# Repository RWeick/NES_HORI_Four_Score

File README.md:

# NES_HORI_Four_Score
The Kicad files for the NES HORI Four Score multitap adapter

PCB Thickness: 1.6 mm

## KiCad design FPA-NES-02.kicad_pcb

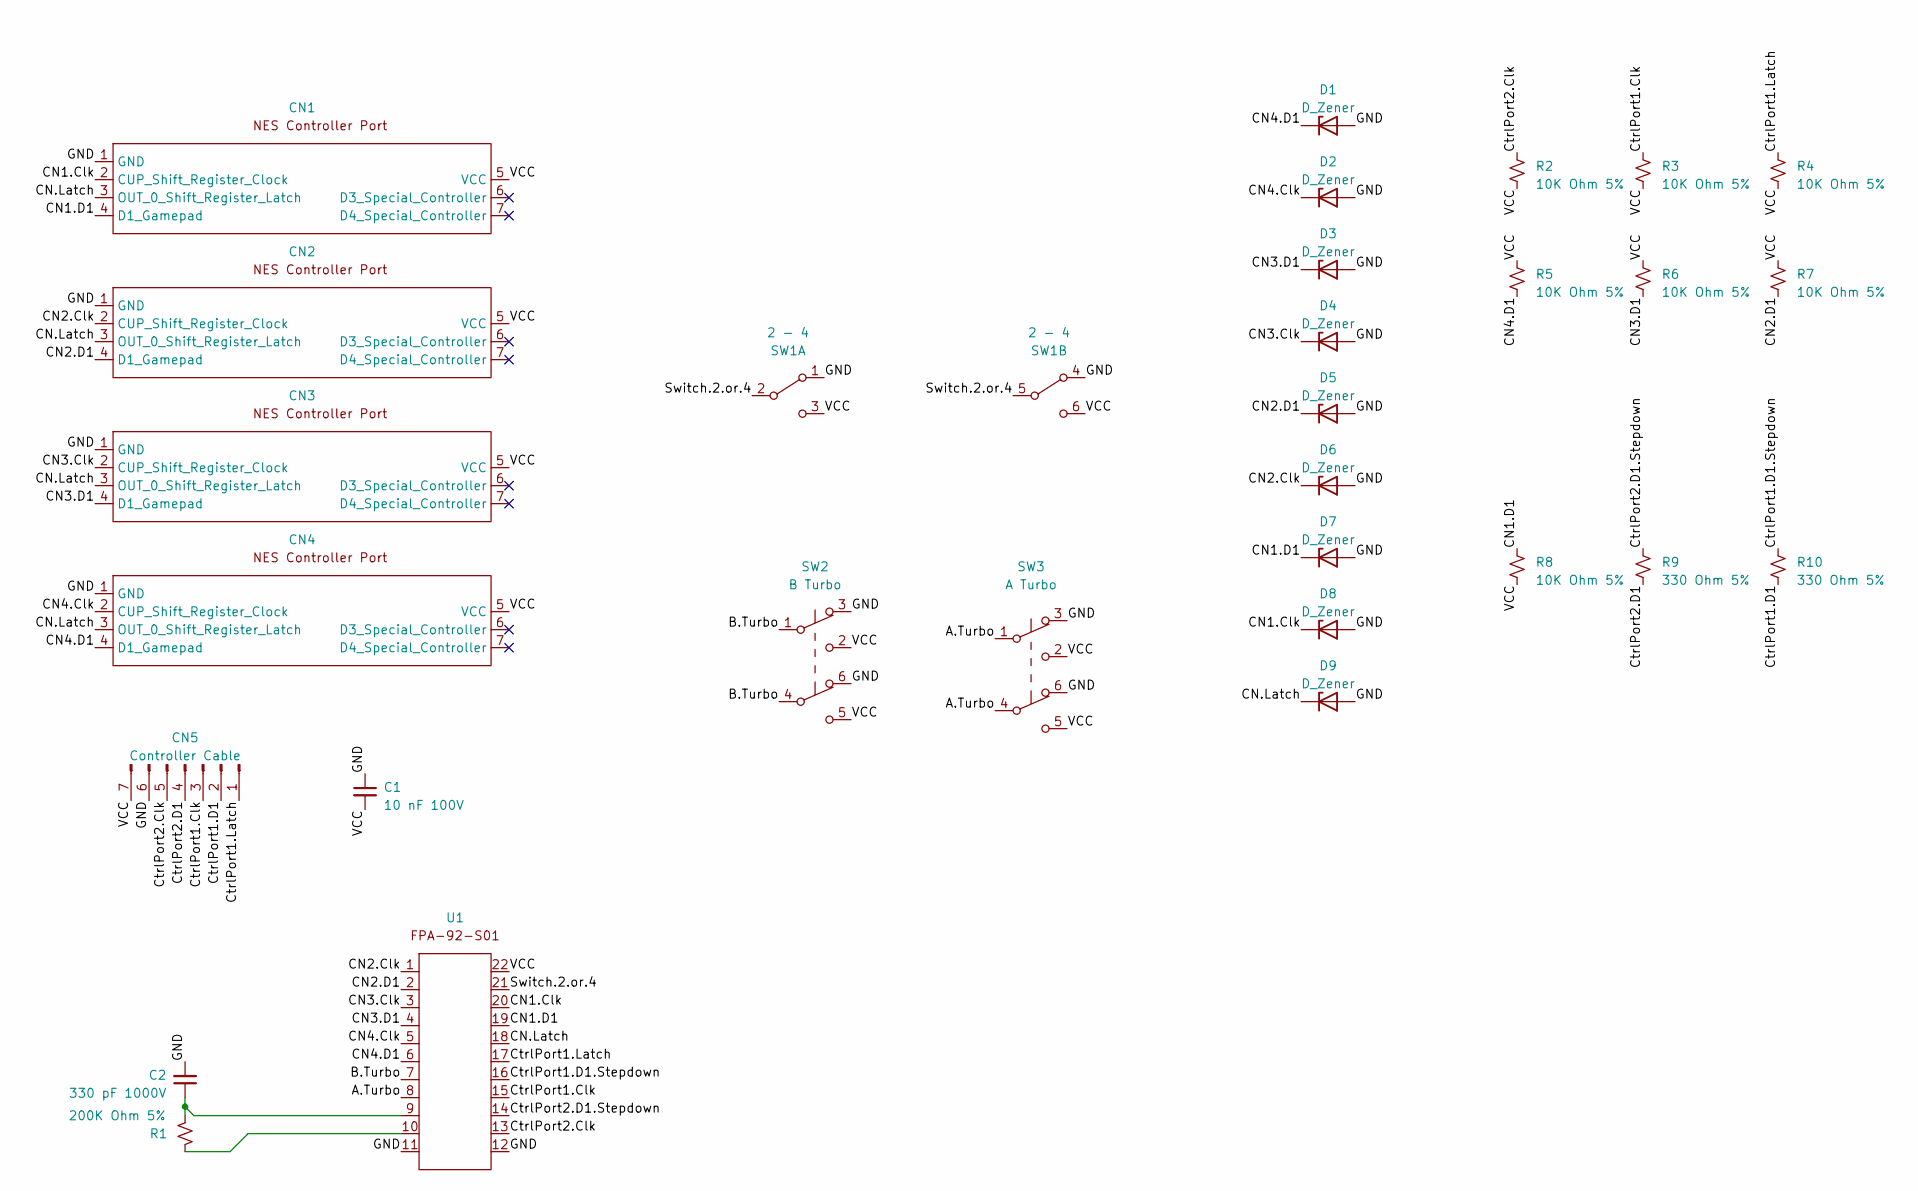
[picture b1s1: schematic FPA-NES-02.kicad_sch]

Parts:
C1: 10 nF 100V; Capacitor
C2: 330 pF 1000V; Capacitor
CN1, CN2, CN3, CN4: NES Controller Port
CN5: Controller Cable; NES Controller Port Connector
D1, D2, D3, D4, D5, D6, D7, D8, D9: D_Zener; Diode
R1: 200K Ohm 5%; Resistor
R2, R3, R4, R5, R6, R7, R8: 10K Ohm 5%; Resistor
R9, R10: 330 Ohm 5%; Resistor
SW1: 2 - 4; Slide Switch
SW2: B Turbo; Push Button Switch
SW3: A Turbo; Push Button Switch
U1: FPA-92-S01

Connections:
/A.Turbo: SW3.1 (B), SW3.4 (B), U1.8
/B.Turbo: SW2.1 (B), SW2.4 (B), U1.7
/CN1.Clk: CN1.2 (CUP_Shift_Register_Clock), D8.1 (K), U1.20
/CN1.D1: CN1.4 (D1_Gamepad), D7.1 (K), R8.1, U1.19
/CN2.Clk: CN2.2 (CUP_Shift_Register_Clock), D6.1 (K), U1.1
/CN2.D1: CN2.4 (D1_Gamepad), D5.1 (K), R7.2, U1.2
/CN3.Clk: CN3.2 (CUP_Shift_Register_Clock), D4.1 (K), U1.3
/CN3.D1: CN3.4 (D1_Gamepad), D3.1 (K), R6.2, U1.4
/CN4.Clk: CN4.2 (CUP_Shift_Register_Clock), D2.1 (K), U1.5
/CN4.D1: CN4.4 (D1_Gamepad), D1.1 (K), R5.2, U1.6
/CN.Latch: CN1.3 (OUT_0_Shift_Register_Latch), CN2.3 (OUT_0_Shift_Register_Latch), CN3.3 (OUT_0_Shift_Register_Latch), CN4.3 (OUT_0_Shift_Register_Latch), D9.1 (K), U1.18
/CtrlPort1.Clk: CN5.3, R3.1, U1.15
/CtrlPort1.D1: CN5.2, R10.2
/CtrlPort1.D1.Stepdown: R10.1, U1.16
/CtrlPort1.Latch: CN5.1, R4.1, U1.17
/CtrlPort2.Clk: CN5.5, R2.1, U1.13
/CtrlPort2.D1: CN5.4, R9.2
/CtrlPort2.D1.Stepdown: R9.1, U1.14
/GND: C1.1, C2.2, CN1.1 (GND), CN2.1 (GND), CN3.1 (GND), CN4.1 (GND), CN5.6, D1.2 (A), D2.2 (A), D3.2 (A), D4.2 (A), D5.2 (A), D6.2 (A), D7.2 (A), D8.2 (A), D9.2 (A), SW1.1 (A), SW1.4 (A), SW2.3 (A), SW2.6 (A), SW3.3 (A), SW3.6 (A), U1.11, U1.12
/Switch.2.or.4: SW1.2 (B), SW1.5 (B), U1.21
/VCC: C1.2, CN1.5 (VCC), CN2.5 (VCC), CN3.5 (VCC), CN4.5 (VCC), CN5.7, R2.2, R3.2, R4.2, R5.1, R6.1, R7.1, R8.2, SW1.3 (C), SW1.6 (C), SW2.2 (C), SW2.5 (C), SW3.2 (C), SW3.5 (C), U1.22
unnamed: C2.1, R1.2, U1.9
unnamed: R1.1, U1.10

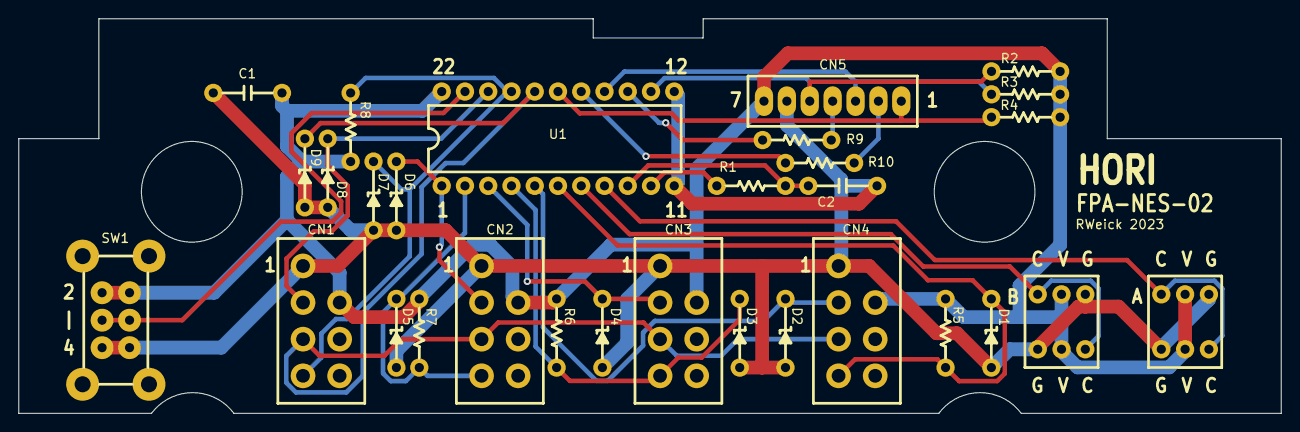
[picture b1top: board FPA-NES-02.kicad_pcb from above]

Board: 2 copper layers, 137.9 x 43.1 mm, 32 parts (0 on the bottom side), 23 nets.

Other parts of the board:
Hole1, Hole2: MountingHole_8.4mm_M8
